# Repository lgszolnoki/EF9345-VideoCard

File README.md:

# EF9345-VideoCard
EF9345 based RCBus compatible video card with VGA output targeting RomWBW. 
I have used the following sources, among others:

[https://github.com/EtchedPixels/FUZIX](https://github.com/EtchedPixels/FUZIX) <br>
[https://stardot.org.uk/forums/viewtopic.php?t=22941](https://stardot.org.uk/forums/viewtopic.php?t=22941)<br>
[https://hackaday.io/project/182424-ef9365-ef9366-ef9367-video](https://hackaday.io/project/182424-ef9365-ef9366-ef9367-video)<br>
[https://hackaday.io/project/189225-80-column-video-for-rc2014](https://hackaday.io/project/189225-80-column-video-for-rc2014)

## Hardware
This simple video card provides a VGA compatible output for 80x24 or 40x24 text display formats. The PCB design is done by Eagle. The board was manufactured by JLCPCB. For the addressing I prefere to use PLDs. Attached the souce code as well as the JEDEC file.
## Software
The card can be configured for a 40x24 or 80x24 text display. However, the resolution of 40x24 is not suitable for RomWBW. The 80x24 resolution is fine for most applications. The software has some problems with the scrolling function.  WS and ZDE show strange behavior when scrolling up linewise, but page up and down works fine. 
### Contributions are welcome to fix the problem.

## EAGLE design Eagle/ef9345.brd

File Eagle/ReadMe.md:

## Eagle
The zip file contains the Gerber file for production.

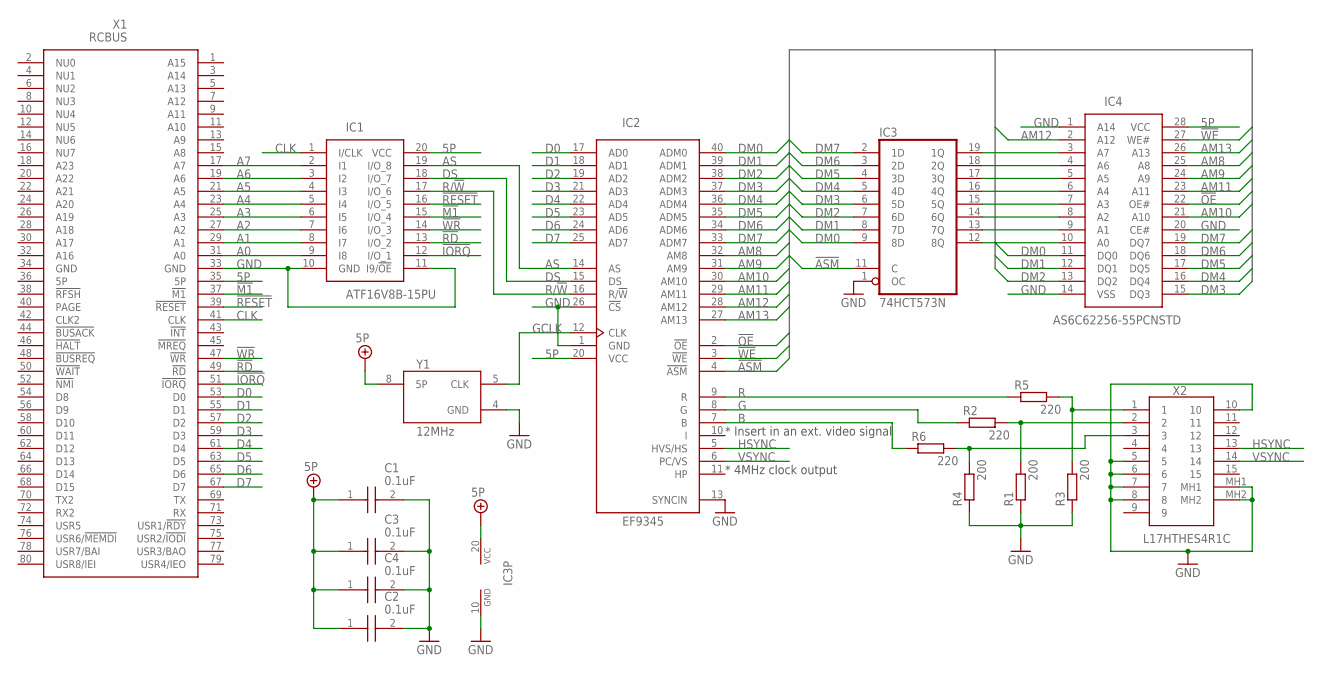
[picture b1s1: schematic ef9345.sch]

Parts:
C1, C2, C3, C4: 0.1uF; K104K15X7RF53H5
IC1: ATF16V8B-15PU; DIP794W59P254L2591H533Q20N
IC2: EF9345; DIL40
IC3: 74HCT573N; DIL20
IC4: AS6C62256-55PCNSTD; DIL28
R1, R3, R4: 200; 0207/10
R2, R5, R6: 220; 0207/10
X1: RCBUS; RC2014_80_RA
X2: L17HTHES4R1C
Y1: 12MHz; ECS-2100AX-200

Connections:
5P: C1.1, C2.1, C3.1, C4.1, IC1.20 (VCC), IC2.20 (VCC), IC3.20 (VCC), IC4.28 (VCC), X1.35 (5P), X1.36 (5P), Y1.8 (5P)
!ASM: IC2.4 (!ASM), IC3.11 (C)
!IORQ: IC1.12 (I/O_1), X1.51 (!IORQ)
!M1: IC1.15 (I/O_4), X1.37 (!M1)
!OE: IC2.2 (!OE), IC4.22 (OE#)
!RD: IC1.13 (I/O_2), X1.49 (!RD)
!RESET: IC1.16 (I/O_5), X1.39 (!RESET)
!WE: IC2.3 (!WE), IC4.27 (WE#)
!WR: IC1.14 (I/O_3), X1.47 (!WR)
A0: IC1.9 (I8), X1.31 (A0)
A1: IC1.8 (I7), X1.29 (A1)
A2: IC1.7 (I6), X1.27 (A2)
A3: IC1.6 (I5), X1.25 (A3)
A4: IC1.5 (I4), X1.23 (A4)
A5: IC1.4 (I3), X1.21 (A5)
A6: IC1.3 (I2), X1.19 (A6)
A7: IC1.2 (I1), X1.17 (A7)
AM8: IC2.32 (AM8), IC4.25 (A8)
AM9: IC2.31 (AM9), IC4.24 (A9)
AM10: IC2.30 (AM10), IC4.21 (A10)
AM11: IC2.29 (AM11), IC4.23 (A11)
AM12: IC2.28 (AM12), IC4.2 (A12)
AM13: IC2.27 (AM13), IC4.26 (A13)
AS: IC1.19 (I/O_8), IC2.14 (AS)
B: IC2.7 (B), R6.1
CLK: IC1.1 (I/CLK), X1.41 (CLK)
D0: IC2.17 (AD0), X1.53 (D0)
D1: IC2.18 (AD1), X1.55 (D1)
D2: IC2.19 (AD2), X1.57 (D2)
D3: IC2.21 (AD3), X1.59 (D3)
D4: IC2.22 (AD4), X1.61 (D4)
D5: IC2.23 (AD5), X1.63 (D5)
D6: IC2.24 (AD6), X1.65 (D6)
D7: IC2.25 (AD7), X1.67 (D7)
DM0: IC2.40 (ADM0), IC3.9 (8D), IC4.11 (DQ0)
DM1: IC2.39 (ADM1), IC3.8 (7D), IC4.12 (DQ1)
DM2: IC2.38 (ADM2), IC3.7 (6D), IC4.13 (DQ2)
DM3: IC2.37 (ADM3), IC3.6 (5D), IC4.15 (DQ3)
DM4: IC2.36 (ADM4), IC3.5 (4D), IC4.16 (DQ4)
DM5: IC2.35 (ADM5), IC3.4 (3D), IC4.17 (DQ5)
DM6: IC2.34 (ADM6), IC3.3 (2D), IC4.18 (DQ6)
DM7: IC2.33 (ADM7), IC3.2 (1D), IC4.19 (DQ7)
DS: IC1.18 (I/O_7), IC2.15 (DS)
G: IC2.8 (G), R2.1
GCLK: IC2.12 (CLK), Y1.5 (CLK)
GND: C1.2, C2.2, C3.2, C4.2, IC1.10 (GND), IC1.11 (I9/!OE), IC2.1 (GND), IC2.13 (SYNCIN), IC2.26 (!CS), IC3.1 (OC), IC3.10 (GND), IC4.1 (A14), IC4.14 (VSS), IC4.20 (CE#), R1.1, R3.1, R4.1, X1.33 (GND), X1.34 (GND), X2.5, X2.6, X2.7, X2.8, X2.10, X2.MH1, X2.MH2, Y1.4 (GND)
HSYNC: IC2.5 (HVS/HS), X2.13
unnamed: IC3.19 (1Q), IC4.3 (A7)
unnamed: IC3.18 (2Q), IC4.4 (A6)
unnamed: IC3.17 (3Q), IC4.5 (A5)
unnamed: IC3.16 (4Q), IC4.6 (A4)
unnamed: IC3.15 (5Q), IC4.7 (A3)
unnamed: IC3.14 (6Q), IC4.8 (A2)
unnamed: IC3.13 (7Q), IC4.9 (A1)
unnamed: IC3.12 (8Q), IC4.10 (A0)
unnamed: R3.2, R5.2, X2.1
unnamed: R1.2, R2.2, X2.2
unnamed: R4.2, R6.2, X2.3
R: IC2.9 (R), R5.1
R/!W: IC1.17 (I/O_6), IC2.16 (R/!W)
VSYNC: IC2.6 (PC/VS), X2.14

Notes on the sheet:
* 4MHz clock output
* Insert in an ext. video signal

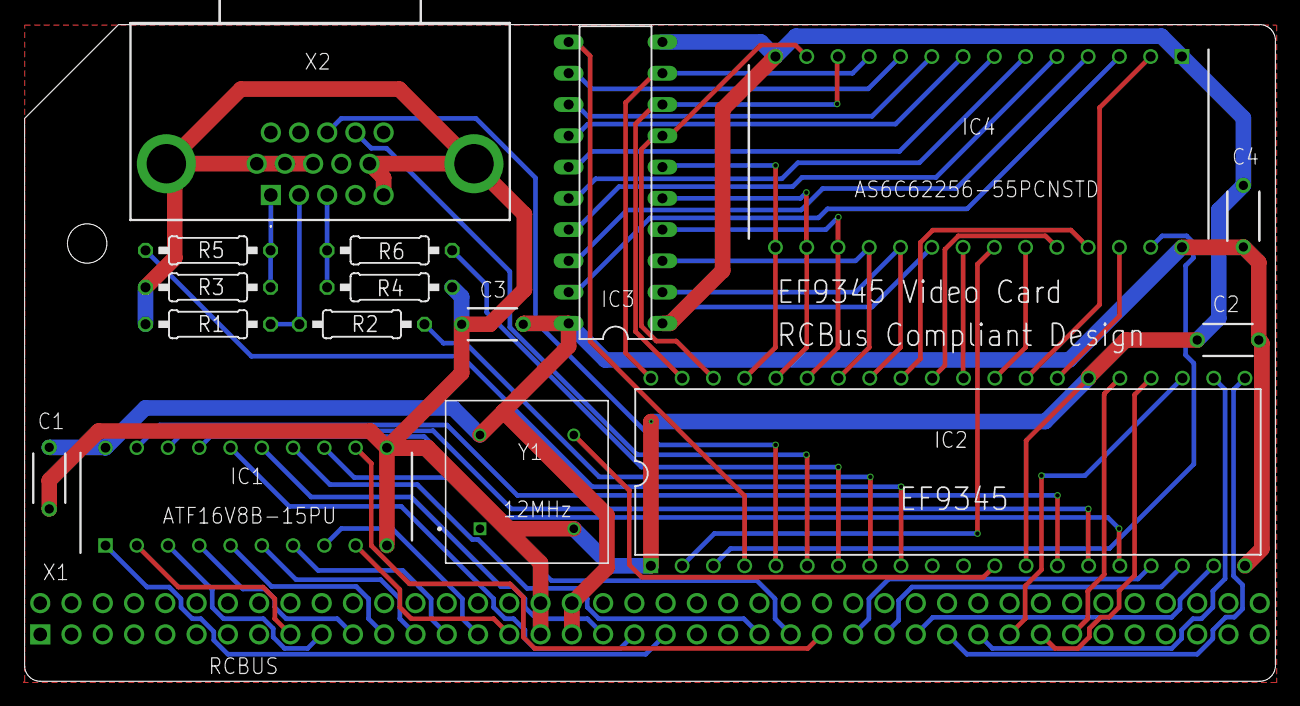
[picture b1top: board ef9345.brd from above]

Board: 2 copper layers, 101.6 x 53.3 mm, 17 parts (0 on the bottom side), 61 nets.

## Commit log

2024-01-22 Create Source
2024-02-04 Source/ef9345.asm
2024-02-04 Rename 68094.asm to 40x24.asm
2024-02-04 Rename 68098.asm to 80x24.asm
2024-02-04 Rename klein.asm to klein40x24.asm
2024-02-04 Rename IMG_6956.jpg to scrollup.jpg
2024-02-11 Add files via upload
    Tested file for RomWBW
2024-02-11 Add files via upload
    Modified base address for RomWBW.
2024-02-11 Update ReadMe.md
    adding ef.asm
